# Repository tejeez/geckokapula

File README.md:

# Gekkokapula
Silicon Labs EFR32 transceivers give access to filtered IQ samples on receive,
so it's possible to make a multimode handheld transceiver using them.

## Features
* Waterfall display (12 kHz wide)
* Receives FM, AM, USB, LSB, CW
* Transmits FM, CW, [USB*](#ssb-transmit), [LSB*](#ssb-transmit)
* Minimalistic user interface with a single knob

## Construction
There are two major versions of the hardware.
The first version is built around a
[BRD4151](https://www.silabs.com/documents/public/reference-manuals/brd4151a-rm.pdf)
radio module and only works in the 2.3-2.9 GHz band.
See [hardware\_v1/](hardware_v1/README.md) for details.

The second version is built on a custom PCB and uses a dual band EFR32 chip.
See [hardware_v2/pcb/](hardware_v2/pcb/) for a KiCad schematic and PCB design.
Construction is documented in [hardware_v2 README file](hardware_v2/README.md).

There is also a [tutorial for flashing firmware](firmware/flashing.md).

## Frequency range for the dual band model
The second version was initially designed for the 70 cm (432 MHz)
and 13 cm (2.3 GHz) amateur radio bands. Later it was found that
the EFR32 can be made to tuner over a much broader range.
Matching circuits of sub-GHz path in current hardware are optimized
for 70 cm but work reasonably well for lower frequencies as well.
Modification for the 23 cm band should be possible but has not
been attempted yet.

Tuning range has some gaps but covers the following frequencies:
* 13.2 - 725 MHz
* 766.7 - 966.6 MHz
* 1.15 - 1.45 GHz
* 2.3 - 2.9 GHz

## SSB transmit

\* SSB is transmitted as a constant envelope signal by only modulating
the frequency of a synthesizer. Amplitude variations are discarded and
the synthesizer is made to approximately track the phase of an SSB
modulated signal. This results is somewhat distorted audio and some
splatter to neighboring channels, but it sounds surprisingly
intelligible and has even received reports of good sound quality.
During quiet moments, some carrier is added in order to have
something to transmit.

Having a slightly dirty spectrum, this SSB transmitting trick
may not be suitable for high transmit power on a crowded bands,
but is probably acceptable for VHF/UHF contacts at low transmit power.

## Licensing

The firmware is released under the [MIT license](firmware/LICENSE).
It depends on the Gecko SDK from Silicon Labs,
mostly licensed under the Zlib license.

I haven't decided on licensing of the hardware design yet.

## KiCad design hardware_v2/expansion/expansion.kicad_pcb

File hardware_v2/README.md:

# Hardware version 2.2

## Overview

The Gekkokapula kit currently includes:
* Gekkokapula PCB v2.2
* Display module
* Pin header for display module
* 2 U.FL-SMA cables

To build a complete radio, you will additionally need:
* Enclosure
* Speaker
* Quadrature encoder (may be added to kit in future)
* Electret microphone (may be added to kit in future)
* 1S Li-Ion (or 3S NiMH) battery
* PTT button (optional)
* Volume potentiometer (optional)
* Power switch (optional)
* Serial Wire Debug adapter (to update firmware)

Most of these parts are connected to header J1 on the Gekkokapula PCB.
Schematic diagram of wiring between header J1 and other parts:

It is a good idea to connect the battery last after connecting
everything else. This reduces the risk of accidental short circuits
during construction.

## Detailed information

### Gekkokapula board
The Gekkokapula PCB contains most of the electronics.
All SMD components are already placed on the board, so
you only need to hand solder some through hole pin headers.
All bigger and more "mechanical" parts are wired to these
pin headers. This lets you choose any enclosure
you like and arrange all the knobs, buttons and connectors
the way you like.

### Display
Solder 8-pin female header to J9 on Gekkokapula board
and plug display module into the header.

The display is a
[128x160 RGB TFT module with an 8-pin header](https://www.ebay.com/itm/403774302965).

These display modules also include an SD card slot
but it is not used for anything in Gekkokapula.
The 4-pin SD card header J10, however, can be placed and used for
additional mechanical support and ground pins.

### Encoder
The most important part of the user interface is a quadrature
encoder with a push button.
Connect one as shown in the wiring diagram above.

### Speaker
Connect a speaker between SPK+ and SPK- pins
(pins 13 and 14 on header J1).
Almost any speaker should work.
A 4 Ω or 8 Ω speaker with a power handling of at least 1 W
is recommended.

Keep in mind that most speakers need an enclosure to work properly.
A small speaker without an enclosure may sound too quiet.

### Microphone
Connect an electret microphone capsule between MIC and GND
(pins 9 and 10 on header J1).
Most electret microphones should work here.

### Battery
The board includes a protection circuit and a charger for a single
cell Li-Ion or Li-Po battery with a nominal voltage of 3.6 or 3.7 V.
For example, a flat cellphone battery or a 18650 cell can be used.

Connect battery between BAT+ and BAT- pins
(pins 17 and 18 on header J1). Note that battery minus is not
directly connected to ground (because of the protection circuit).

Although designed for Lithium batteries, the circuit also works
with 3 NiMH cells in series, since their voltages are
[close enough](https://www.ti.com/lit/an/slyt468/slyt468.pdf)
to 1S Li-Ion.

### Charging
The battery charger works with any supply voltage from 4 V to 9 V
between VCharge pin and GND (pins 19 and 20 on header J1).

5 V from a USB port or a cellphone charger works fine.

### RF connections
All RF connectors on the board are U.FL. Use pigtail cables
to adapt them to your favourite RF connectors.

13 cm band has its own connector, J3. It is used for
receiving and transmitting in the 2300-2900 MHz range.
All lower frequency bands (13 MHz to 1.45 GHz) use the
connector J5.

J4 is not connected by default but the board can be
[modified to make it an RX connector](#separate-connectors-for-rx-and-tx).

J6 (CLKOUT) is currently unused but may be used in future as a reference
frequency output for transverters.

## Optional parts

### PTT button
A PTT button is optional since transmitting can be also started
from the "menu" using the encoder.

If you prefer to have a dedicated button for PTT, connect one
between PTT and GND (pins 11 and 12 on header J1).

### Power switch
A power switch is optional since there is software and hardware
support for a sleep mode which reduces current consumption
to a few µA.

If you prefer to have a "real" power switch, connect a toggle
switch between PWSW pins (pins 15 and 16 on header J1).

If a switch is not used, connect pins 15 and 16 directly together.

### Volume potentiometer
A volume potentiometer is optional since volume can be also
adjusted from the "menu" using the encoder.

If you prefer to have a dedicated knob for volume, connect
a potentiometer between pins 5, 6 and 7 on header J1
as illustrated on the silkscreen.
Resistance of the potentiometer should be something from
10 kΩ to 50 kΩ.

If a potentiometer is not connected, connect pins 5 and 6
together. Volume can be also reduced by adding a fixed
series resistor or a voltage divider here.

## Bugs
PCB v2.1 has its RF switch control lines swapped.
This can be fixed by moving series resistors
R76 and R77 to cross the lines.
This has been fixed in version 2.2.

Sometimes the board does not power up after battery has been
connected. Seems like the battery protection chip ends up in
some state where it disconnects the battery. If this happens,
try momentarily shorting GND and BAT- together to bypass the
protection circuit. Usually it starts working and keeps working
as long as battery is kept connected.

Silkscreen marking of one expansion header pin in wrong in
both v2.1 and v2.2: pin 2 of J2 is marked as GND but is
actually connected to VBAT.

## Advanced use and modifications

### Updating firmware and debugging
The EFR32 chip on the board is flashed through
Serial Wire Debug (SWD). The board has a 10-pin header with
[Cortex Debug standard pinout](https://documentation-service.arm.com/static/5fce6c49e167456a35b36af1)
but using 2.54 mm pitch instead of the standard 1.27 mm pitch
(to make it easier to solder wires or connectors to it).

GND, SWCLK and SWDIO pins are required and shall be connected to
corresponding pins on your SWD adapter.

The VDD pin is an output meant for SWD adapters with a reference
voltage input (used for level shifters or target detection).
If your SWD adapter does not have a reference voltage input,
leave the VDD pin unconnected. Using this VDD pin to supply power
to the Gekkokapula board is not recommended.

If your SWD adapter has a 5 V output pin, it can be used to supply
power to the board by connecting 5 V to pin 16 on J1
(power switch pin).
If you have a battery connected, you can also connect 5 V
to pin 19 on J1 (VCharge) to charge the battery.

Any SWD adapter supported by OpenOCD should work but may need
additional configuration for OpenOCD.
I can try to add configuration for more adapters
if you can give me an adapter to test with.

See [flashing tutorial](../firmware/flashing.md) for details
on installation and use of flashing software.

### Using without battery
If you want to directly use an external power supply and bypass
battery protection and charging circuits, connect the supply
between power switch VBAT pin (pin 16 on J1) and ground
(such as pin 20 on J1).

The circuit can handle supply voltages from 3 V to 6 V.
Keep in mind that a higher voltage will result in higher power
dissipation in 3.3 V regulator and audio amplifier chips.
Recommended range is between 3.5 V and 5.0 V to keep voltage
regulator working and to keep its dissipation reasonable.

### Headphone connector
Output of the audio power amplifier is bridged, so neither end of
the speaker is connected to ground.

If you want to add a headphone jack, it may be more convenient to
connect one end of headphones to ground, particularly if you use
a 4-pin headset connector with a microphone pin. This can be done
but an additional DC blocking capacitor is needed.
Series resistors are also recommended to protect the audio amplifier
from short circuits.

TODO: diagram showing additional circuitry for a headphone jack

### Use on bands other than 13 cm and 70 cm
The board includes a low-pass filter (LPF) for the 70 cm band.
This is needed to suppress transmitter harmonics and receiver
harmonic mixing products.
RF matching circuits are also optimized for 70 cm but will
work on other bands with somewhat reduced transmit power
and receive sensitivity.

For use on other bands, the LPF should be bypassed
(by moving C82 and R78) and an external LPF should be
connected between J5 and an antenna.
Receiving lower bands without modification or external
filtering is possible but the receiver is prone to harmonic
mixing if a proper LPF is not used. This means you may hear
spurious responses from higher frequencies, such as
FM broadcast signals when trying to listen to HF,
or 70cm band signals when trying to listen to 2m.

### Separate connectors for RX and TX
J4 can be used as a separate receiving connector for frequencies
below 1.45 GHz. This can be useful with an external power amplifier,
low noise amplifier or a transverter.
To use J4, move capacitor C74 to connect receiving chain to J4
through TP5 (and to disconnect it from the RX/TX switch).

On 2300-2900 MHz, J3 is always used for both TX and RX.
Separate connectors for 13 cm are not available.

### Changing charging current
Charge current is limited to approximately 400 mA.
If you want to change the current limit, check the
[data sheet of the charger chip](https://datasheetspdf.com/pdf-file/1090540/NanJingTopPower/TP4054/1)
and change resistor R2 value.

### Expansion header
Header J2 gives access to different supply voltages,
TX/RX switch controls and some free EFR32 pins.
These could be used to control an additional power amplifier
or switched band filters. No such expansions exist at the moment
but they might be developed in the future.

During transmission, TX_EN (pin 19) is high (at 3.3 V) and
RX_EN pin (pin 17) is low (at 0 V).
During reception, TX_EN is low and RX_EN is high.
These pins can be used to control an external power amplifier
and RX/TX switching.

VDD (pin 3) is directly connected to output of a 3.3 V regulator
that powers most of the components on the board.
VDDS (pin 5) is VDD through a power switch that turns off when
the board is in sleep mode. These pins can be used to supply
a few tens of milliamperes for external logic.

DVDD (pin 7) is the output from an EFR32 internal switching
regulator used to supply some parts of the EFR32 chip.
Powering external circuits from this pin is not recommended
since maximum current draw has not been determined yet.

VBAT (pins 1 and 2) are battery voltage output pins.
These can be used to supply an external power amplifier.

PA0, PA1, PB11 and PB12 are free for use by expansion boards.
PB11 and PB12 might be used in future for an I2C bus.
For example, an I2C I/O expander could be used to add more I/O
pins to control a band switch.
PA0 and PA1 were used for an UART in some old firmware versions
but the pins are currently unused.

PA2 is connected on the board for battery voltage measurement
and PA5 for battery charge detection. These features are currently
unimplemented in firmware, so the pins have been brought to the
header to allow using them for other purposes as well.
If you want to use them for something else, remove jumpers
R1 (for PA5) and R13 (for PA2) from the board.

Free EFR32 pins could be even used to interface some external
sensors or a computer, allowing some "IoT" or "modem" kind of
applications. I have no plans for such expansions at the moment
but anything is possible. Feel free to experiment!

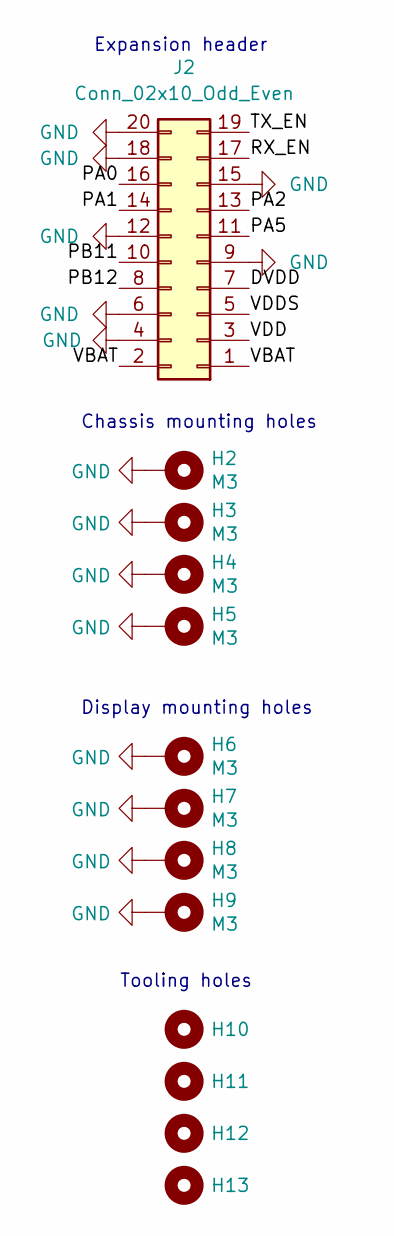
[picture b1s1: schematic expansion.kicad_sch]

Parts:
H2, H3, H4, H5, H6, H7, H8, H9: M3; MountingHole_3.2mm_M3_Pad
H10, H11, H12, H13: ToolingHole
J2: Conn_02x10_Odd_Even; PinHeader_2x10_P2.54mm_Vertical

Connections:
/DVDD: J2.7
/PA0: J2.16
/PA1: J2.14
/PA2: J2.13
/PA5: J2.11
/PB11: J2.10
/PB12: J2.8
/RX_EN: J2.17
/TX_EN: J2.19
/VBAT: J2.1, J2.2
/VDD: J2.3
/VDDS: J2.5
GND: H2.1, H3.1, H4.1, H5.1, H6.1, H7.1, H8.1, H9.1, J2.4, J2.6, J2.9, J2.12, J2.15, J2.18, J2.20

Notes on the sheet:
Expansion header
Chassis mounting holes
Tooling holes
Display mounting holes

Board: 4 copper layers, 13 parts (0 on the bottom side), 2 nets, no tracks yet.

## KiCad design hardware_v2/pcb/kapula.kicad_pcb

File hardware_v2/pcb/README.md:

# Circuit and PCB design for hardware version 2.2

The PCB is designed so that all SMD components can be placed by
[JLCPCB](https://jlcpcb.com/).

Tutorials for ordering:
* [How to generate Gerber and Drill files in KiCad 7](https://jlcpcb.com/help/article/362-how-to-generate-gerber-and-drill-files-in-kicad-7)
* [How to generate the BOM and Centroid file from KiCAD](https://jlcpcb.com/help/article/81-How-to-generate-the-BOM-and-Centroid-file-from-KiCAD)

Make sure each component gets placed in the right orientation.
Pin 1 of each IC is marked with a dot on the silkscreen.

## Settings for JLCPCB Standard PCB/PCBA

* PCB Qty: 30
* Surface Finish: LeadFree HASL
* Specify Layer Sequence: Yes, F / In1 / In2 / B
* Impedance Control: Yes, JLC046161H-7628 (Prepreg thickness 0.2104 mm)
* Remove Order Number: Specify a location
* PCB Assembly: Yes
* Tooling holes: Added by Customer

## Component placement corrections

* U.FLs: Rotate right, move 4 steps
* U1: Rotate (forgot how much)
* U4: Rotate right
* U2, U3, U7, Q1, Q2, Q3, Q4, Q5, Q6: Rotate 180°

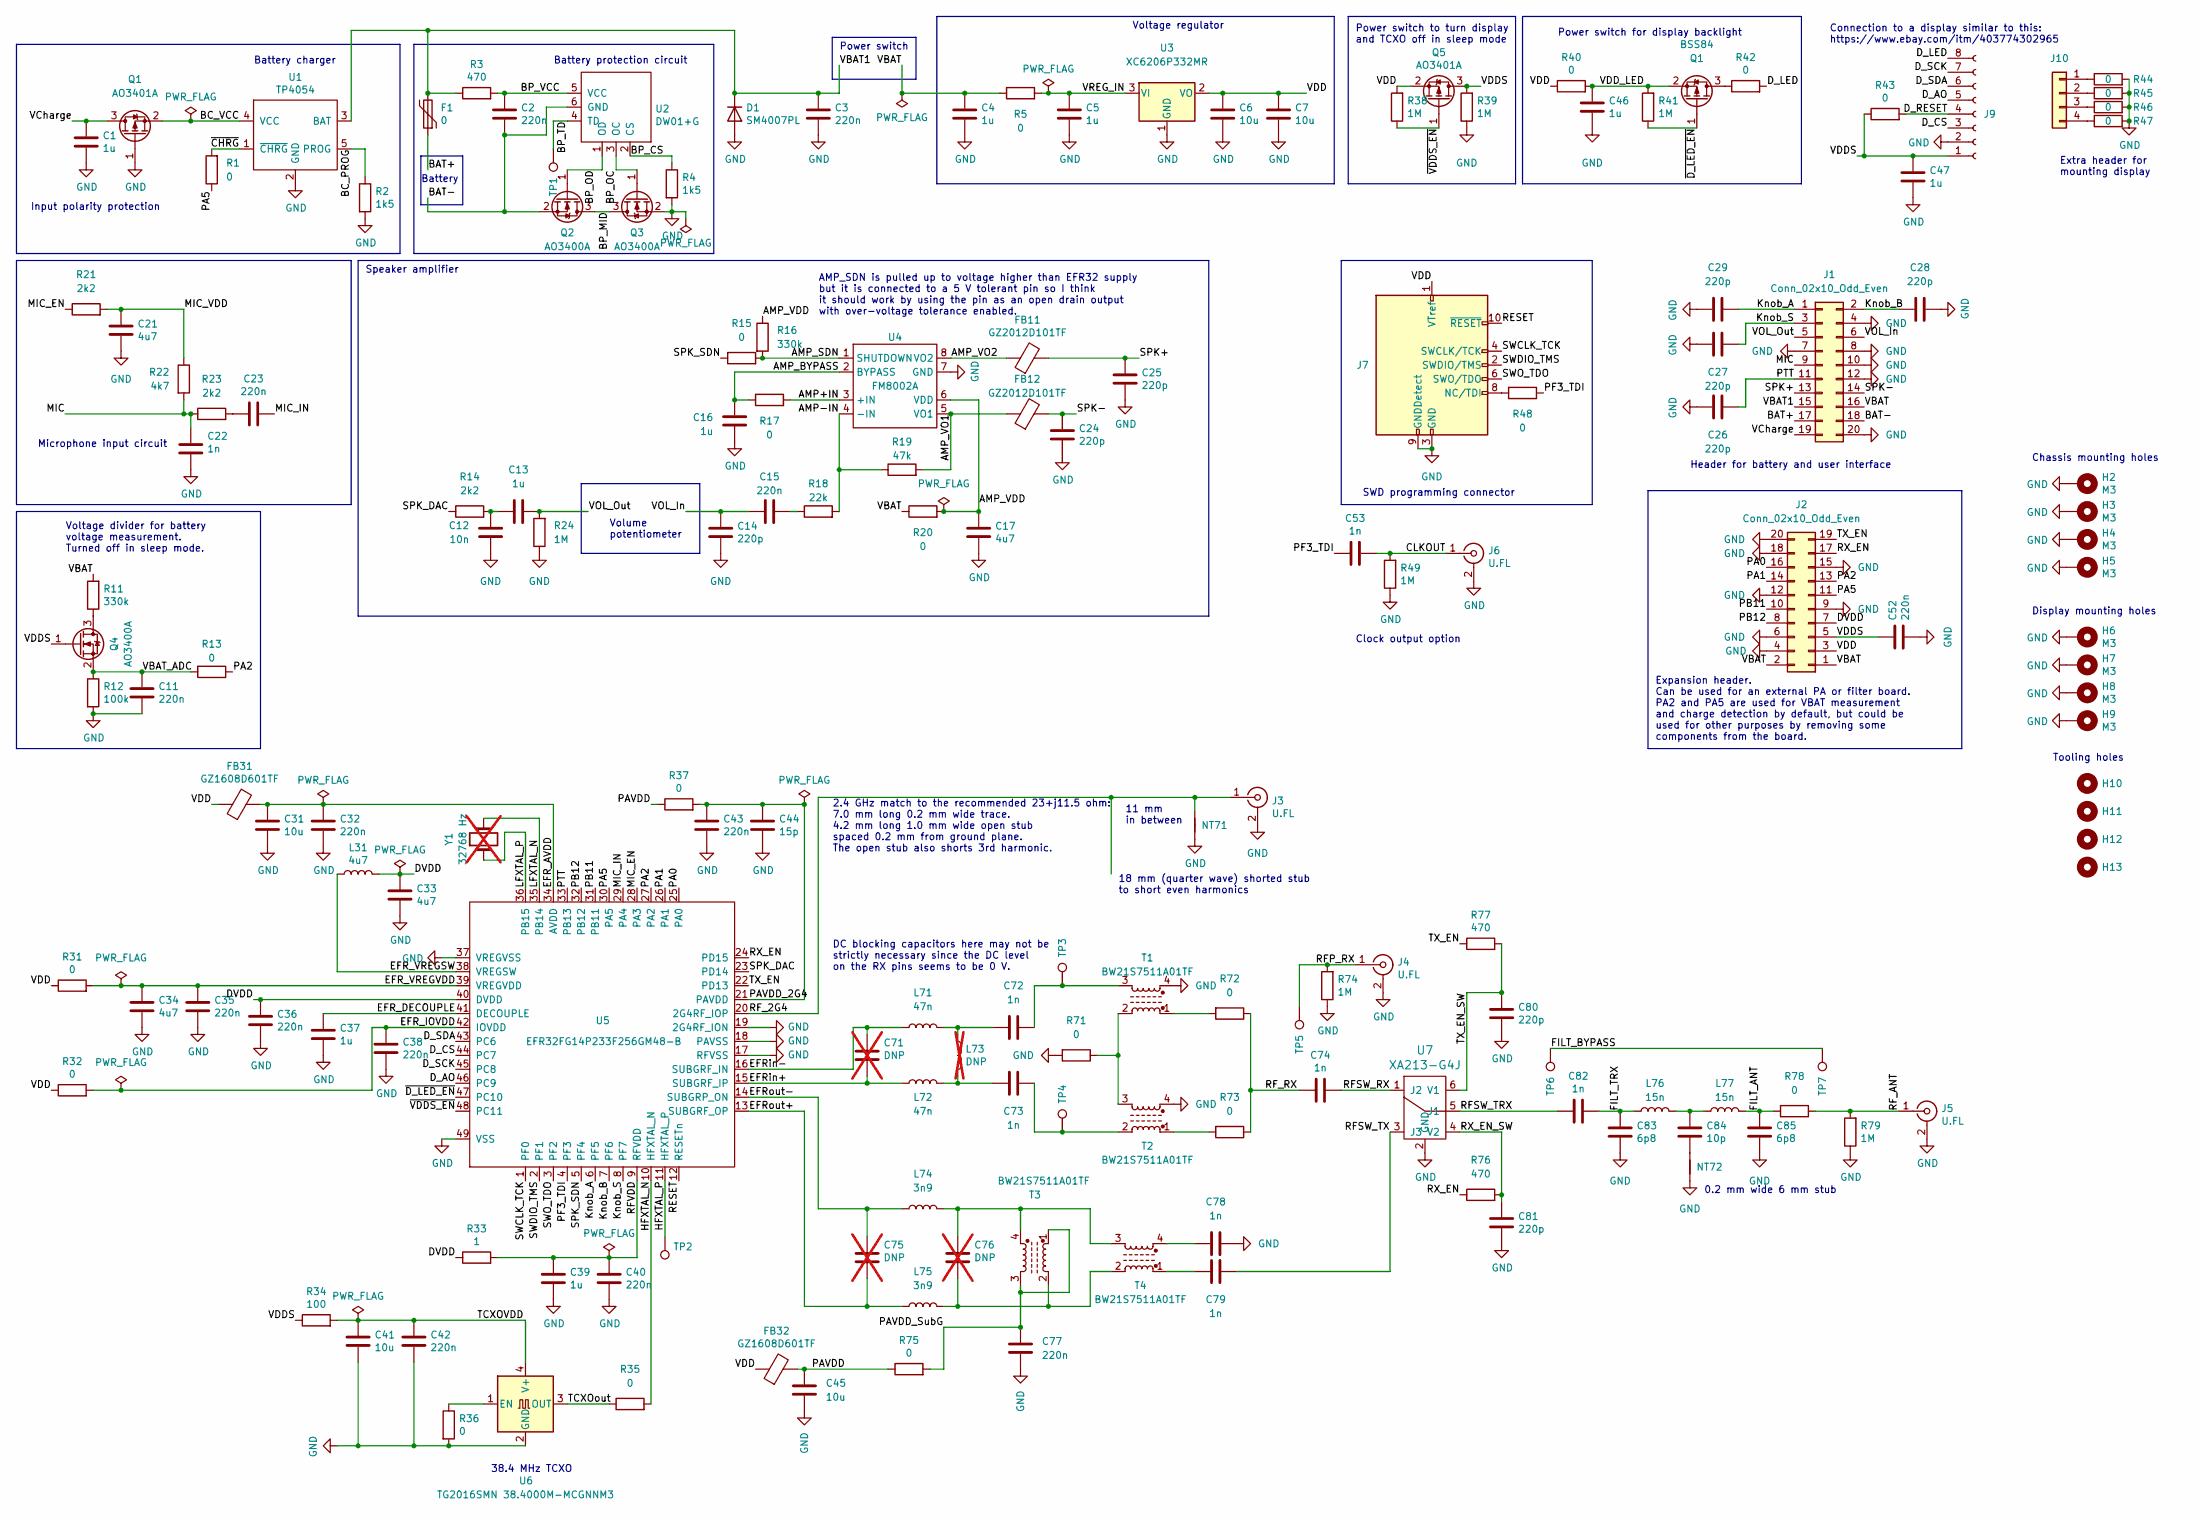
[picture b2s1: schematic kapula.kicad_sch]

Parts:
C1, C4, C5, C13, C16, C37, C39, C46, C47: 1u; C_0603_1608Metric; LCSC C15849
C2, C3, C11, C23, C32, C35, C36, C38, C40, C42, C43, C52, C77: 220n; C_0402_1005Metric; LCSC C16772
C6, C7, C31, C41, C45: 10u; C_0805_2012Metric; LCSC C15850
C12: 10n; C_0402_1005Metric; LCSC C15195
C14, C24, C25, C26, C27, C28, C29, C80, C81: 220p; C_0402_1005Metric; LCSC C1530
C15: 220n; C_0402_1005Metric_Pad0.74x0.62mm_HandSolder; LCSC C16772
C17, C21, C33, C34: 4u7; C_0805_2012Metric; LCSC C1779
C22, C53, C72, C73, C78, C79: 1n; C_0402_1005Metric; LCSC C1523
C44: 15p; C_0402_1005Metric; LCSC C1548
C71: DNP; C_0402_1005Metric; not fitted
C74, C82: 1n; C_0603_1608Metric_Pad1.08x0.95mm_HandSolder; LCSC C1588
C75, C76: DNP; C_0402_1005Metric_Pad0.74x0.62mm_HandSolder; not fitted
C83, C85: 6p8; C_0603_1608Metric_Pad1.08x0.95mm_HandSolder; LCSC C1679
C84: 10p; C_0603_1608Metric_Pad1.08x0.95mm_HandSolder; LCSC C1634
D1: SM4007PL; D_SOD-123F; LCSC C64898
F1: 0; R_1206_3216Metric_Pad1.30x1.75mm_HandSolder; LCSC C17888
FB11, FB12: GZ2012D101TF; L_0805_2012Metric_Pad1.05x1.20mm_HandSolder; LCSC C1015
FB31, FB32: GZ1608D601TF; L_0603_1608Metric_Pad1.05x0.95mm_HandSolder; LCSC C1002
H2, H3, H4, H5, H6, H7, H8, H9: M3; MountingHole_3.2mm_M3_Pad
H10, H11, H12, H13: ToolingHole
J1, J2: Conn_02x10_Odd_Even; PinHeader_2x10_P2.54mm_Vertical
J3, J4, J5, J6: U.FL; U.FL_Hirose_U.FL-R-SMT-1_Vertical; LCSC C88374
J7: PinHeader_2x05_P2.54mm_Vertical
J9: PinSocket_1x08_P2.54mm_Vertical
J10: PinSocket_1x04_P2.54mm_Vertical
L31: 4u7; L_1206_3216Metric; LCSC C1049
L71, L72: 47n; L_0402_1005Metric_Pad0.77x0.64mm_HandSolder; LCSC C27151
L73: DNP; L_0402_to_0603_HandSolder; not fitted
L74, L75: 3n9; L_0402_1005Metric_Pad0.77x0.64mm_HandSolder; LCSC C14033
L76, L77: 15n; L_0402_1005Metric_Pad0.77x0.64mm_HandSolder; LCSC C27143
NT71: NetTie-2_SMD_Pad0.3mm
NT72: NetTie-2_SMD_Pad0.2mm
Q1, Q5: AO3401A; SOT-23; LCSC C15127
Q2, Q3, Q4: AO3400A; SOT-23; LCSC C20917
R1, R5, R13, R35, R44, R45, R46, R47, R48, R78: 0; R_0603_1608Metric_Pad0.98x0.95mm_HandSolder; LCSC C21189
R2: 1k5; R_0603_1608Metric_Pad0.98x0.95mm_HandSolder; LCSC C22843
R3, R76, R77: 470; R_0402_1005Metric; LCSC C25117
R4: 1k5; R_0603_1608Metric; LCSC C22843
R11: 330k; R_0402_1005Metric_Pad0.72x0.64mm_HandSolder; LCSC C25778
R12: 100k; R_0402_1005Metric_Pad0.72x0.64mm_HandSolder; LCSC C25741
R14, R21, R23: 2k2; R_0402_1005Metric; LCSC C25879
R15, R17, R20, R31, R32, R36, R37, R40, R42, R43, R71, R72, R73, R75: 0; R_0402_1005Metric; LCSC C17168
R16: 330k; R_0402_1005Metric; LCSC C25778
R18: 22k; R_0603_1608Metric_Pad0.98x0.95mm_HandSolder; LCSC C31850
R19: 47k; R_0603_1608Metric_Pad0.98x0.95mm_HandSolder; LCSC C25819
R22: 4k7; R_0402_1005Metric; LCSC C25900
R24, R38, R39, R41, R49, R74, R79: 1M; R_0402_1005Metric; LCSC C26083
R33: 1; R_0603_1608Metric_Pad0.98x0.95mm_HandSolder; LCSC C22936
R34: 100; R_0603_1608Metric_Pad0.98x0.95mm_HandSolder; LCSC C22775
T1, T2, T3, T4: BW21S7511A01TF; BW21S; LCSC C138776
TP1, TP2, TP5, TP6, TP7: Pad_1mm
TP3, TP4: Pad_0402_1005Metric
U1: TP4054; SOT-23-5_HandSoldering; LCSC C32574
U2: DW01+G; SOT-23-6_Handsoldering; LCSC C14213
U3: XC6206P332MR; SOT-23; LCSC C5446
U4: FM8002A; SOP-8_3.9x4.9mm_P1.27mm; LCSC C94625
U5: EFR32FG14P233F256GM48-B; QFN-48-1EP_7x7mm_P0.5mm_EP5.3x5.3mm
U6: TG2016SMN 38.4000M-MCGNNM3; TG2016SMN; LCSC C1987359
U7: XA213-G4J; SOT-363_SC-70-6; LCSC C556294
Y1: 32768 Hz; Crystal_SMD_3215-2Pin_3.2x1.5mm; not fitted

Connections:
/AMP+IN: R17.2, U4.3 (+IN)
/AMP-IN: R18.2, R19.1, U4.4 (-IN)
/AMP_BYPASS: C16.1, R17.1, U4.2 (BYPASS)
/AMP_SDN: R15.2, R16.2, U4.1 (SHUTDOWN)
/AMP_VDD: C17.1, R16.1, R20.2, U4.6 (VDD)
/AMP_VO1: FB12.1, R19.2, U4.5 (VO1)
/AMP_VO2: FB11.1, U4.8 (VO2)
/BAT+: F1.1, J1.17
/BAT-: C2.2, J1.18, Q2.2 (S), U2.6 (GND)
/BC_PROG: R2.1, U1.5 (PROG)
/BP_CS: R4.1, U2.2 (CS)
/BP_MID: Q2.3 (D), Q3.3 (D)
/BP_OC: Q3.1 (G), U2.3 (OC)
/BP_OD: Q2.1 (G), U2.1 (OD)
/BP_TD: TP1.1, U2.4 (TD)
/BP_VCC: C2.1, R3.2, U2.5 (VCC)
/CLKOUT: C53.2, J6.1 (In), R49.2
/DVDD: C33.1, C36.1, J2.7, L31.2, R33.1, U5.40 (DVDD)
/D_AO: J9.5, U5.46 (PC9)
/D_CS: J9.3, U5.44 (PC7)
/D_LED: J9.8, R42.2
/D_RESET: J9.4, R43.2
/D_SCK: J9.7, U5.45 (PC8)
/D_SDA: J9.6, U5.43 (PC6)
/EFR_AVDD: C31.1, C32.1, FB31.2, U5.34 (AVDD)
/EFR_DECOUPLE: C37.1, U5.41 (DECOUPLE)
/EFR_IOVDD: C38.1, R32.2, U5.42 (IOVDD)
/EFR_VREGSW: L31.1, U5.38 (VREGSW)
/EFR_VREGVDD: C34.1, C35.1, R31.2, U5.39 (VREGVDD)
/EFRin+: C71.2, L72.1, U5.15 (SUBGRF_IP)
/EFRin-: C71.1, L71.1, U5.16 (SUBGRF_IN)
/EFRout+: C75.2, L75.2, U5.13 (SUBGRF_OP)
/EFRout-: C75.1, L74.2, U5.14 (SUBGRP_ON)
/FILT_ANT: C85.1, L77.2, R78.2
/FILT_BYPASS: TP6.1, TP7.1
/FILT_TRX: C82.1, C83.1, L76.1
/HFXTAL_N: R35.2, U5.10 (HFXTAL_N)
/HFXTAL_P: TP2.1, U5.11 (HFXTAL_P)
/Knob_A: C29.1, J1.1, U5.6 (PF5)
/Knob_B: C28.1, J1.2, U5.7 (PF6)
/Knob_S: C27.1, J1.3, U5.8 (PF7)
/LFXTAL_N: U5.35 (PB14), Y1.2
/LFXTAL_P: U5.36 (PB15), Y1.1
/MIC: C22.1, J1.9, R22.2, R23.1
/MIC_EN: R21.1, U5.28 (PA3)
/MIC_IN: C23.1, U5.29 (PA4)
/MIC_VDD: C21.1, R21.2, R22.1
/PA0: J2.16, U5.25 (PA0)
/PA1: J2.14, U5.26 (PA1)
/PA2: J2.13, R13.1, U5.27 (PA2)
/PA5: J2.11, R1.1, U5.30 (PA5)
/PAVDD: C45.1, FB32.2, R37.1, R75.1
/PAVDD_2G4: C43.1, C44.1, R37.2, U5.21 (PAVDD)
/PAVDD_SubG: C77.1, R75.2, T3.1, T3.3
/PB11: J2.10, U5.31 (PB11)
/PB12: J2.8, U5.32 (PB12)
/PF3_TDI: C53.1, R48.1, U5.4 (PF3)
/PTT: C26.1, J1.11, U5.33 (PB13)
/RESET: J7.10 (~RESET), U5.12 (RESETn)
/RFP_RX: J4.1 (In), R74.2, TP5.1
/RFSW_RX: C74.1, U7.1 (J2)
/RFSW_TRX: C82.2, U7.5 (J1)
/RFSW_TX: C79.1, U7.3 (J3)
/RFVDD: C39.1, C40.1, R33.2, U5.9 (RFVDD)
/RF_2G4: J3.1 (In), NT71.1, U5.20 (2G4RF_IOP)
/RF_ANT: J5.1 (In), R78.1, R79.2
/RF_RX: C74.2, R72.1, R73.1
/RX_EN: J2.17, R76.1, U5.24 (PD15)
/RX_EN_SW: C81.1, R76.2, U7.4 (V2)
/SPK+: C25.1, FB11.2, J1.13
/SPK-: C24.1, FB12.2, J1.14
/SPK_DAC: R14.1, U5.23 (PD14)
/SPK_SDN: R15.1, U5.5 (PF4)
/SWCLK_TCK: J7.4 (SWCLK/TCK), U5.1 (PF0)
/SWDIO_TMS: J7.2 (SWDIO/TMS), U5.2 (PF1)
/SWO_TDO: J7.6 (SWO/TDO), U5.3 (PF2)
/TCXOVDD: C41.1, C42.1, R34.2, U6.4 (V+)
/TCXOout: R35.1, U6.3 (OUT)
/TX_EN: J2.19, R77.1, U5.22 (PD13)
/TX_EN_SW: C80.1, R77.2, U7.6 (V1)
/VBAT: C4.1, J1.16, J2.1, J2.2, R5.1, R11.2, R20.1
/VBAT1: C3.1, D1.1 (K), F1.2, J1.15, R3.1, U1.3 (BAT)
/VBAT_ADC: C11.1, Q4.2 (S), R12.1, R13.2
/VDD: C6.1, C7.1, FB31.1, FB32.1, J2.3, J7.1 (VTref), Q5.2 (S), R31.1, R32.1, R38.2, R40.1, U3.2 (VO)
/VDDS: C47.1, C52.1, J2.5, J9.1, Q4.1 (G), Q5.3 (D), R34.1, R39.2, R43.1
/VOL_In: C14.1, C15.1, J1.6
/VOL_Out: C13.2, J1.5, R24.2
/VREG_IN: C5.1, R5.2, U3.3 (VI)
/~CHRG: R1.2, U1.1 (~CHRG)
/~VDDS_EN: Q5.1 (G), R38.1, U5.48 (PC11)
unnamed: C12.1, C13.1, R14.2
unnamed: C15.2, R18.1
unnamed: C23.2, R23.2
unnamed: C72.1, T1.3, TP3.1
unnamed: C72.2, L71.2, L73.1
unnamed: C73.1, T2.2, TP4.1
unnamed: C73.2, L72.2, L73.2
unnamed: C76.1, L74.1, T3.4, T4.3
unnamed: C76.2, L75.1, T3.2, T4.2
unnamed: C78.2, T4.4
unnamed: C79.2, T4.1
unnamed: C84.1, L76.2, L77.1
unnamed: C84.2, NT72.1
unnamed: J7.8 (NC/TDI), R48.2
unnamed: J10.1, R44.1
unnamed: J10.2, R45.1
unnamed: J10.3, R46.1
unnamed: J10.4, R47.1
unnamed: Q4.3 (D), R11.1
unnamed: R71.1, T1.2, T2.3
unnamed: R72.2, T1.1
unnamed: R73.2, T2.1
unnamed: R36.1, U6.1 (EN)

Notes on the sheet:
Voltage regulator
SWD programming connector
Battery protection circuit
Header for battery and user interface
Input polarity protection
11 mm in between
Tooling holes
AMP_SDN is pulled up to voltage higher than EFR32 supply but it is connected to a 5 V tolerant pin so I think it should work by using the pin as an open drain output with over-voltage tolerance enabled.
DC blocking capacitors here may not be strictly necessary since the DC level on the RX pins seems to be 0 V.
38.4 MHz TCXO
Battery charger
Battery
Display mounting holes
Volume potentiometer
Speaker amplifier
0.2 mm wide 6 mm stub
Power switch
Connection to a display similar to this: https://www.ebay.com/itm/403774302965
Clock output option
Microphone input circuit
Chassis mounting holes
2.4 GHz match to the recommended 23+j11.5 ohm: 7.0 mm long 0.2 mm wide trace. 4.2 mm long 1.0 mm wide open stub spaced 0.2 mm from ground plane. The open stub also shorts 3rd harmonic.
Voltage divider for battery voltage measurement. Turned off in sleep mode.
Extra header for mounting display
18 mm (quarter wave) shorted stub to short even harmonics
Power switch to turn display and TCXO off in sleep mode
Power switch for display backlight
Expansion header. Can be used for an external PA or filter board. PA2 and PA5 are used for VBAT measurement and charge detection by default, but could be used for other purposes by removing some components from the board.

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
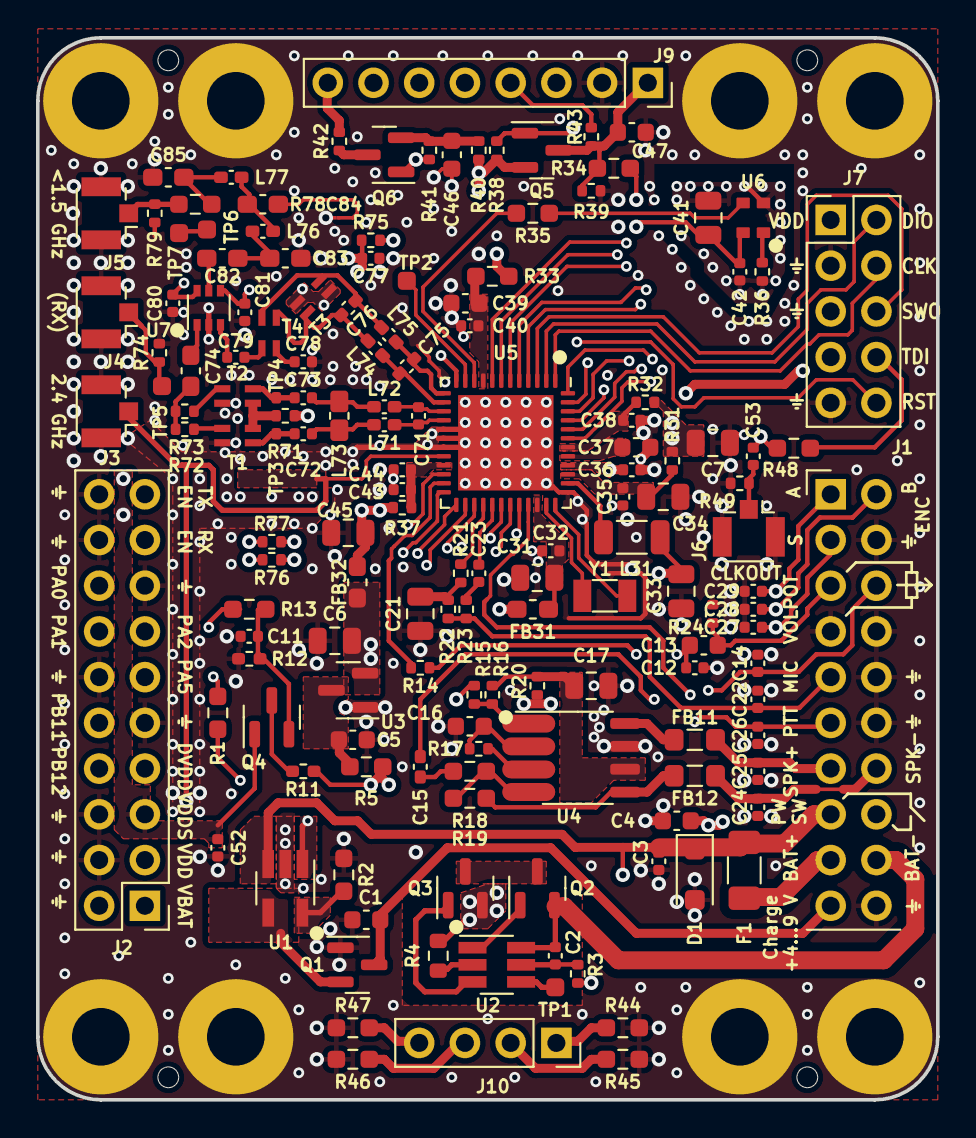
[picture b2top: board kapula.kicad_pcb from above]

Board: 4 copper layers, 50.0 x 59.0 mm, 166 parts (0 on the bottom side), 119 nets.

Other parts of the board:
Q6: BSS84; SOT-23

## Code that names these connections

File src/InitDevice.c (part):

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
	// $[Port A Configuration]

	/* Pin PA0 is configured to Push-pull */
	GPIO_PinModeSet(gpioPortA, 0, gpioModePushPull, 0);

	/* Pin PA1 is configured to Input enabled with filter */
	GPIO_PinModeSet(gpioPortA, 1, gpioModeInput, 1);
	// [Port A Configuration]$

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
	// $[Port C Configuration]

	/* Pin PC6 is configured to Push-pull */
	GPIO_PinModeSet(gpioPortC, 6, gpioModePushPull, 0);

	/* Pin PC7 is configured to Push-pull */
	GPIO_PinModeSet(gpioPortC, 7, gpioModePushPull, 1);

	/* Pin PC8 is configured to Push-pull */
	GPIO_PinModeSet(gpioPortC, 8, gpioModePushPull, 0);

	/* Pin PC9 is configured to Push-pull */
	GPIO_PinModeSet(gpioPortC, 9, gpioModePushPull, 0);

	/* Pin PC10 is configured to Push-pull */
	GPIO_PinModeSet(gpioPortC, 10, gpioModePushPull, 1);
	// [Port C Configuration]$

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	/* Pin PD12 is configured to Input enabled with pull-up */
	GPIO_PinModeSet(gpioPortD, 12, gpioModeInputPull, 1);

	/* Pin PD13 is configured to Input enabled with pull-up */
	GPIO_PinModeSet(gpioPortD, 13, gpioModeInputPull, 1);
	// [Port D Configuration]$

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
	// $[Port F Configuration]

	/* Pin PF3 is configured to Input disabled with pull-up */
	GPIO_PinModeSet(gpioPortF, 3, gpioModeDisabled, 1);

	/* Pin PF4 is configured to Push-pull */
	GPIO_PinModeSet(gpioPortF, 4, gpioModePushPull, 0);

	/* Pin PF5 is configured to Push-pull */
	GPIO_PinModeSet(gpioPortF, 5, gpioModePushPull, 1);

	/* Pin PF6 is configured to Input enabled with pull-up */
	GPIO_PinModeSet(gpioPortF, 6, gpioModeInputPull, 1);
	// [Port F Configuration]$

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
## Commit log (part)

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2017-09-22 Created project
2017-09-22 Generated code. It compiles
2017-09-22 Trying to make it do something
2017-09-24 Trying to control display (not working)
2017-09-24 Display works
2017-11-26 TX works now: RADIO_PA_Init was missing
2017-11-26 FM receiver and CW transmitter working
2017-11-26 Spectrogram display works now
    There was a buffer overflow bug in reading RX fifo
    because of fixed buffer size forgotten as a parameter.
    arm_cfft_f32 also needed bitReverseFlag=1
    for non-bit-reversed ordering of output.
2017-11-26 Some documentation in README
2017-11-29 Add audio LPF, remove display test
2017-11-30 Implement text in UI
2017-11-30 Some UI improvements
    Also put RAIL idle before changing frequency to avoid crash
2017-12-03 Use quadrature decoder in timer peripheral, refactored UI code to use it
2017-12-03 Use DMA for SPI, UI improvements
    Also enabled ADC peripheral which is going to be used
2017-12-18 FreeRTOS compiles
2017-12-18 FreeRTOS works, running two tasks as a test
2017-12-19 Put math defines in ISC file
    This could work better when configuration is generated after importing the project
2018-01-08 Test modulation by RAIL frequency override, UI fixes
2018-03-24 Some random changes to UI
2018-03-25 Fix priorities to let RAIL task run
2018-03-25 Waterfall scrolling and rotated UI by 90°
2018-03-25 Slight refactoring and cleanup
2018-03-26 Add AM RX
2018-03-26 Trying to find out what the radio registers do
2018-03-28 FM transmit experiment
2018-03-31 Waterfall averaging and some optimization
    It does not look very smooth yet. Looks like DSP interrupt is already
    taking a bit too much CPU because setting demodulation to none
    makes the waterfall go much faster.
2018-03-31 DMA closer to working correctly but not yet
2018-03-31 DMA almost working?
    PWM DMA works for a couple of cycles now and then stops.
    It worked better at some point but now with RAIL in use again something broke.
2018-04-01 Trying something with DMA
2018-04-02 Add some more debug prints and other hacks to see if transfers remain synchronized with each other
    They don't. ADC DMA seems to sometimes miss more samples than synth DMA
    so they go out of sync.
    Also PWM DMA occassionally misses some samples causing RAIL FIFO to fill up.
    Also tried using SYNC DMA descriptor to synchronize ADC and synth.
    It does sort of work, regularly starting the cycles in sync but
    still does not look that good.
2018-07-21 Add squelch and improve TX audio
2020-03-20 Move code under firmware/
2020-03-20 Change float ABI to softfp to allow using RAIL
2020-03-21 RAIL 2 port: RX and TX working
    Frequency cannot be changed yet
2020-03-21 Cleanup. Remove unnecessary generated files.
2020-03-22 Receive signal processing works again
2020-03-23 Rearrange various things a bit
    - Changing frequency works now
    - Move user interface input to another task
    - Use semaphore to trigger FFT calculation
2020-03-24 Improve display drawing task
    Get rid of polling in the display task and use a semaphore instead.
2020-03-24 Start implementing SSB
    Unfinished. I have to get more familiar with biquad filters.
2020-03-24 Some cleanup, add S-meter
2020-03-25 Add a separate RAIL configurator project
2020-05-25 PCB: Add some part numbers and circuit details
2020-05-25 PCB: Attempt some layout for RF parts
2020-05-26 PCB: Place components approximately in layout
2020-05-27 PCB: Add some connectors and more routing
2020-05-27 PCB: Route display and knob traces
2020-05-27 PCB: Everything routed
2020-05-27 PCB: More clear BOM, some changes
2020-06-30 Fix pinout bugs. Add radio configuration for v2 model.
2020-09-23 Add a separate minimal firmware to debug why v2 doesn't receive
2020-09-23 rxdebug: Try some things
    Change the order of RAIL calls. Now it matches another project I checked.
    With a different value, even SetRxFifoThreshold now seems to succeed.
    Also tried implementing RAILCb_SetupRxFifo.
    It gets called, but it didn't seem to change anything.
2020-09-30 Test sub-GHz on v2
    It's fixed on sub-GHz now, so this version doesn't work on 2.4 GHz.
2022-08-07 Fix default frequency for 2.4 GHz single band models
2022-08-07 Fix pinout bugs for v1 model
2022-08-09 Improve documentation, organize files
2022-08-11 PCB: Add new RF matching ideas
2022-08-12 Test changing intermediate frequency
    This commit shows how the intermediate frequency (IF)
    parameter affects the values in the RAIL configuration table.
    I found the old Simplicity Studio installation
    that was used to generate the previous configuration.
    I verified it still generated exactly
    the same RAIL configuration values.
2022-08-12 Test changing designed RF frequency
    This is similar to the previous commit but this time changing
    the base frequency the RAIL configuration is generated for.
2022-08-12 Fix frequencies for v1
2022-08-13 Add power off mode
    Hardware was also modified a bit.
    TCXO is now powered through the same load switch as the display.
    This simplifies both hardware and software by eliminating the need
    for a separate TCXO enable pin.
2022-08-14 PCB: Miscellaneous circuit updates
2022-08-14 PCB: Layout switching regulator
2022-08-17 PCB: Misc layout work
2022-08-17 PCB: Improve EFR decoupling layout
2022-08-17 PCB: Add possible 2.4 GHz layout
2022-08-18 PCB: Maybe this is a better 2.4 GHz layout after all
2022-08-23 PCB: Some RF layout and power supply details
2023-03-02 Add OpenOCD scripts
    These were already written in Aug 14 2022
    but had not been committed yet.
2023-03-02 Add parts of Gecko SDK needed to compile the firmware
    The code can be now compiled without having that old version
    of Simplicity Studio installed.
2023-03-07 PCB: Update to KiCad 7.0
2023-03-16 Test using internal opamp as microphone amplifier
    Opamp output is now temporarily on PF3 and ADC input on PF2
    for testing purposes.
    Input is still on PA2 but R18 and Q4 should be removed
    from the old circuit to make the input AC coupled.
2023-05-26 Improve transmit audio, move power-off to mode menu
2023-05-26 Increase transmit deviation a bit
2023-07-19 Add switches for backlight and VBAT_ADC, pinout updates
2023-08-22 Update and add component values and part numbers
2023-08-22 Reduce PCB size
    Remove footprints for encoder, battery holder and such from the board.
    They will be connected by wires to a pin header instead.
2023-08-22 Some routing
2023-08-22 Organize layout, a bit more routing
2023-08-23 Roughly place some power supply related components in layout
2023-08-24 PCB: Organize RF layout
2023-08-24 PCB: Route some display and connector lines
2023-08-24 PCB: Organize lowpass components to fit them on board again
2023-08-24 PCB: Route TX lowpass again
2023-08-24 PCB: Rearrange 2.4 GHz matching
    TODO: check that its dimensions are correct
2023-08-25 PCB: Miscellaneous routing
2023-08-26 PCB: More miscellaneous routing
2023-08-27 PCB: Route audio signals more
2023-08-27 PCB: Route more power supply lines
2023-08-28 PCB: More routing around EFR
2023-08-28 PCB: Change TCXO to a more available one
2023-08-28 PCB: Try to make space for clock out connector
2023-08-29 PCB: Improve some routing
2023-08-29 PCB: Finally managed to route PF4 and VDDS to connector
2023-08-29 PCB: Move connector filtering components
2023-08-29 PCB: Organize components in layout
2023-08-30 PCB: Move some signals to different EFR32 pins
    I think this may give more possibilities for expansions.
2023-09-04 PCB: Some routing for new pinout
2023-09-07 PCB: Place silkscreen texts
2023-09-07 PCB: Route almost everything
    It still needs some cleanup
2023-09-07 PCB: Fix some DRC errors
2023-09-07 PCB: Improve ground via placement and ground fills
2023-09-07 PCB: Fix programming header footprint
2023-09-08 PCB: Some layout cleanup
2023-09-12 PCB: Add more silkscreen texts, some other fixes
2023-09-12 PCB: Fix inductor value in lowpass filter
2023-09-12 PCB: Modify lowpass to use inductors from JLC basic series
2023-09-13 PCB: Move lowpass components more away from display signals
2023-09-14 PCB: Make some planes and fills more continuous
2023-09-16 PCB: Move some vias away from pads a bit
2023-09-16 PCB: Move some silkscreen markings
2023-09-16 PCB: Organize schematic a bit more
2023-09-16 PCB: Fix bug in VBAT_ADC circuit
2023-09-16 PCB: Move some vias to reduce gaps in planes
2023-09-16 PCB: Some small changes
2023-09-17 PCB: Fix some component values and part numbers for fabrication
2023-09-24 PCB: Add information on stackup and assembly
2023-09-24 Organize files, add hardware documentation
2023-09-24 Document display and RF connections
2023-09-26 Add unmodulated carrier transmit support
    I did this too in May 28th already but forgot to commit.
2023-09-26 Invert backlight control for hardware v2.1
2023-09-26 Document more connections and RX/TX bug
2023-09-27 Make wiring diagram more clear
2023-09-29 Use DAC for audio output, change pinout for v2.1
2023-09-30 Add semaphore for RAIL task, cleanup code a bit
2023-09-30 Select the right PA for each band, change default frequency
2023-09-30 Setup more debugging tools
2023-10-03 Document flashing better
2023-10-09 Add vscode extension recommendations
2023-10-09 Make naming of files and hardware versions more consistent
2023-10-10 Add DSP CPU use to diagnostics struct
2023-10-10 Use a timer to produce TX sample rate
2023-10-12 Fix microphone input configuration
2023-10-12 Fix Makefile
    .bin was not always updated after compiling,
    so change dependencies a bit.
    Also add forgotten .PHONY targets.
2023-11-20 Add repeater split in user interface
2023-11-21 Extend tuning range by removing VCO range checks
2023-11-22 Optimize VCO divider calculation
2023-11-22 Implement mode specific UI fields
2023-11-22 Implement multiple text colors
2023-11-24 Add CW and LSB modes
2023-11-25 Fix DSP test program, add modulated I/Q output to it
2023-11-25 Refactor TX DSP
    Move common input audio processing and mode specific processing
    to different functions.
2023-11-25 Start implementing SSB transmit
    This is an initial version that does not fully work
    and has not been adjusted to sound particularly good yet.
    Results from test program sound intelligible
    but real hardware gives somehow different results.
    More debugging will be needed.
2023-11-26 Improve atan2f approximation
2023-11-26 Try to improve SSB TX audio
2023-11-27 Improve SSB filtering
2023-11-27 Fix TX sample rate
2023-12-18 PCB: Remove fill under F1
2023-12-18 PCB: Fix TCXO model in schematic
2024-01-09 PCB: Optimize lowpass filter
    * Reduce second harmonic stub length by 1 mm
    to move notch frequency closer to 870 MHz.
    * Use footprints of correct size for capacitors and inductors.
2024-01-10 PCB: Improve battery charger cooling by adding zones for all pins
2024-01-10 PCB: Move a via that was very close to EFR32 pad
2024-01-10 PCB: Change version number in silkscreen
2024-01-10 PCB: Make some space for TCXO again
2024-01-11 PCB: Fix some silkscreen texts
2024-01-18 PCB: Move connectors exactly to grid
2024-01-26 PCB: Commit some changes
2024-01-26 PCB: Cleanup layout around TCXO
2024-02-11 Fix display initialization
    Send MADCTL command (Memory Data Access Control)
    to make sure display memory is in the correct order.
    This fixes a problem with some displays where the order seems
    to get a random value if it is not set.
    Also add a 120 ms delay suggested in ST7735 datasheet.
2024-02-20 PCB: Rename net 1V8 to DVDD
2024-02-26 Document expansion header and SSB TX
2024-03-05 PCB: Copy holes and header to expansion board, link to schematic
2024-03-05 PCB: Improve expansion board outline
2024-03-05 Expansion PCB: Add 4-layer stackup and ground planes
2024-03-05 Expansion PCB: Improve outline again

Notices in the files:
src/InitDevice.c:
Set up CC0
$[TIMER0 CC0 init]
$[TIMER1 CC0 init]
